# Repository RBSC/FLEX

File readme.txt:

--------------------------------------------
MSX FLEX Slot Extender v1.1
Copyright (c) 2019 RBSC
--------------------------------------------
Last updated: June 14, 2019
--------------------------------------------

WARNING! To avoid damage to FLEX and your MSX computer never insert or remove the extender when a computer is powered on!

WARNING! The extender is not designed to supply the power to more than one cartridge. If a slot expander is connected to
FLEX, it must have its own power supply!

IMPORTANT NOTE! The RBSC can not be sure that FLEX will work flawlessly with all available MSX hardware. See the "Known
issues" section below for more info.

About
-----

The device is the simple extender of the 50-pin MSX slot or MSX bus. It consists of 3 parts - the cartridge part, the 50-pin
slot extender and the 60-pin slot extender modules. The modules are connected to each other with the 50-wire ribbon cable
that is approximately 30cm long. 

The data lines have 100 Ohm resistors installed to compensate for the wave impedance of the ribbon cable. A few 100nf ceramic
capacitors are installed between the +5v and ground signals to remove the possible interferences in power lines.

The FLEX is designed to be used with one cartridge or one 60-pin module at a time. The cartridge board has 2 placeholders
for 50-pin ribbon cable connectors and this allows to attach 2 cables at the same time and to connect the 50 and 60-pin
extenders simultaneously. But those must never have 2 devices inserted at the same time! Doing this may create conflicts and
cause a power surge!

Cases
-----

The models of the cases and their covers must be printed with 0.2mm layer height and with their open sides facing upwards. The
pin is printed vertically and then is glued into the 50-pin extender's case. Brim is recommended for all models. The supports
must be at 20%. The infill must be not lower than 25%. The sturdy PLA is recommended for the cases.

The cartridge module's cover is attached to its case with 2 conical head screws (2.0mm x 12.0mm). The extender modules' covers
are attached to their cases with 4 conical head screws (3.0mm x 20.0mm). Shorter and longer screws must not be used. The screws
could be bought in any decent hardware store.

Engraving
---------

When the cases are printed in black plastic, the "MSX FLEX" text will not be visible on the top of the cases. In this case we
recommend to do laser engraving. The images for laser engraving are attached. The recommended width of the engraving should
not exceed 60mm. The recommended depth of engraving should be 0.1mm. See the "ready_engraved.jpg" picture for the reference.

The engraving must not be done in the areas where the "MSX FLEX" test is present, see the "ready.jpg" image for the reference.
Engraving in the areas where the text is located will result in damaging the thin layer of plastic above the letters and ruin
the good look of the case!

Notes
-----

The boards inside the cartridge case and the 60-pin extender case may wobble a bit. This was designed like that on purpose.
Please do not try to fix the boards firmly. Such wobbling makes the insertion and removal of the cables and devices safer.

Please note that the ribbon cable's connector is made out of plastic, so it's relatively fragile. When pulling the cable out
of the cartridge module please be gentle and do not pull too hard. When removing the cable please try to avoid bending of
the pins on the cartridge board. If the pins are bent, try to carefully straighten them with pliers before inserting the
cable.

The key on the flat ribbon's 50-pin connector may not be compatible with MSX bus expansion connectors of certain MSX computers.
So if you are connecting FLEX to the expansion bus connector, please make sure that the cable's connector is properly aligned.
In some cases the key will need to be removed for the proper alignment, however we advise against it. Be warned, that incorrect
orientation of the FLEX connector may cause severe damage to your MSX computer!

The cases of FLEX modules are normally made out of PLA plastic that is rather fragile. So when disassembling and reassembling
the cases please do not tighten the screws too much or you risk to damage the threads inside the screw holes. If that happens,
fixing the problem would require inserting a few thin threads of PLA into the hole before using the screw.

The SW1 and SW2 pins on the extender modules are not connected to each other. So on MSXs that require those pins to be
shortened in order to enable the power supply, inserting the FLEX with any of its slot extenders will not power-up the computer.
Only when a cartridge or a side slot module is inserted into one of the extender modules, the computer will power-up.

Known issues
------------

The FLEX may not work 100% reliably with all available MSX hardware. We've tested it on Yamaha, Philips, Panasonic, Sanyo and
Toshiba computers and there were a few minor issues that were depending on the hardware of those MSX machines or/and the
devices used in the extender.

We noticed the problem on certain computers with OPLL playback with the GR8NET cartridge. And we had a total failure of FLEX
with RBSC's IDE-FDD cartridge on all MSXs. This cartridge with the Sunrise BIOS complained about data corruption with most of
our CF cards. With other cards it worked, but frequent crashes occurred. So we don't recommend to use FLEX with the IDE-FDD
cartridge.

Tools
-----

The following IDC crimping tool should be used to make the cables:
https://www.aliexpress.com/item/Flat-Ribbon-Cable-Connector-Fixture-IDC-Crimping-Tool-DIY/32792508854.html

The tool requires the special adapter for the male IDC connectors:
https://www.ebay.de/itm/2pc-Adaptor-for-IDC-DIP-Plug-Crimping-tool-HT-214D-Crimper-Width-0-1-0-3-0-6/131173729141

Or you can print the adapter yourself:
https://www.thingiverse.com/thing:3504332

IMPORTANT!
----------

The RBSC provides all the files and information for free, without any liability (see the disclaimer.txt file). The provided
information, software or hardware must not be used for commercial purposes unless permitted by the RBSC. Producing a small
amount of boards for personal projects and selling the rest of the batch is allowed without the permission of RBSC. Printing
of cases is allowed without limitation.

When the boards and 3D models are used to create alternative projects, please always mention the original source and the
copyright!

Contact information
-------------------

The members of RBSC group Wierzbowsky, Tnt23, Ptero, Pencioner and DJS3000 can be contacted via the MSX.ORG or ZX-PK.RU forums.
Just send a personal message and state your business.

The RBSC repository can be found here:

https://github.com/rbsc

The MSX-related 3D models published by RBSC can be found here:

https://www.thingiverse.com/groups/rbsc/things

-= ! MSX FOREVER ! =-

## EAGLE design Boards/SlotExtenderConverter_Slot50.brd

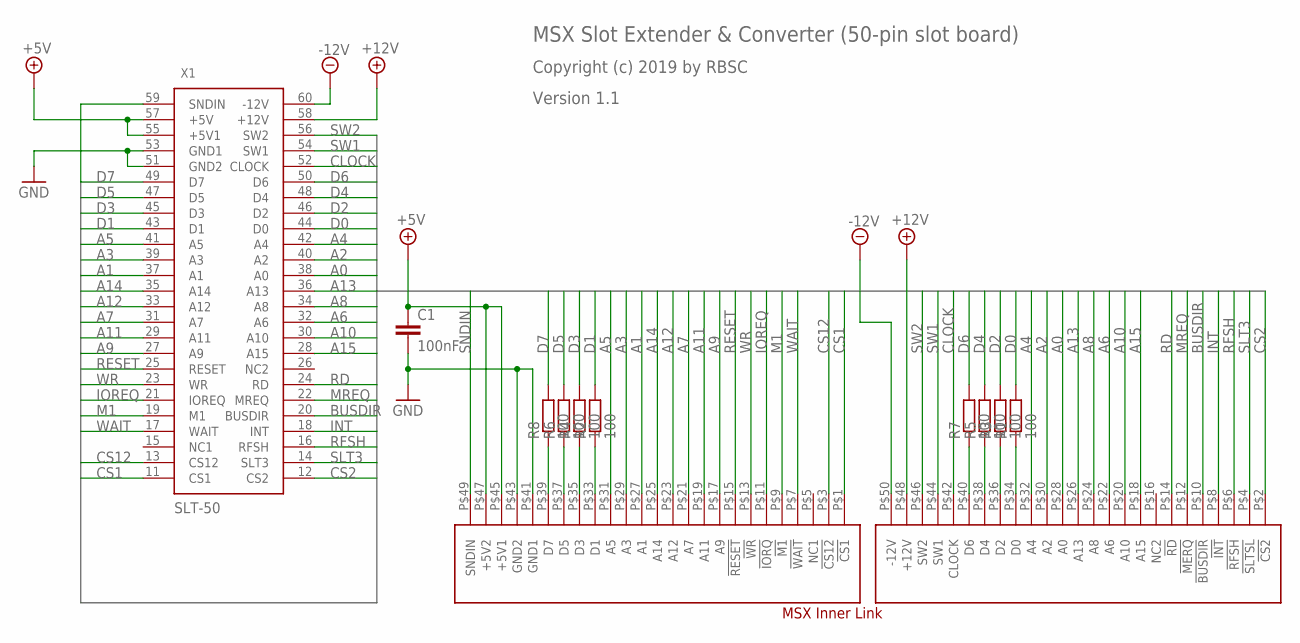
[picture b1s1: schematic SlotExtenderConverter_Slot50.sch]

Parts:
C1: 100nF; C0805K
CN3: MSX_INNER_LINK
R1, R2, R3, R4, R5, R6, R7, R8: 100; M0805
X1: SLT-50

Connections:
+5V: C1.1, CN3.P$45 (+5V1), CN3.P$47 (+5V2), X1.55 (+5V1), X1.57 (+5V)
+12V: CN3.P$48 (+12V), X1.58 (+12V)
-12V: CN3.P$50 (-12V), X1.60 (-12V)
A0: CN3.P$28 (A0), X1.38 (A0)
A1: CN3.P$27 (A1), X1.37 (A1)
A2: CN3.P$30 (A2), X1.40 (A2)
A3: CN3.P$29 (A3), X1.39 (A3)
A4: CN3.P$32 (A4), X1.42 (A4)
A5: CN3.P$31 (A5), X1.41 (A5)
A6: CN3.P$22 (A6), X1.32 (A6)
A7: CN3.P$21 (A7), X1.31 (A7)
A8: CN3.P$24 (A8), X1.34 (A8)
A9: CN3.P$17 (A9), X1.27 (A9)
A10: CN3.P$20 (A10), X1.30 (A10)
A11: CN3.P$19 (A11), X1.29 (A11)
A12: CN3.P$23 (A12), X1.33 (A12)
A13: CN3.P$26 (A13), X1.36 (A13)
A14: CN3.P$25 (A14), X1.35 (A14)
A15: CN3.P$18 (A15), X1.28 (A15)
BUSDIR: CN3.P$10 (!BUSDIR), X1.20 (BUSDIR)
CLOCK: CN3.P$42 (CLOCK), X1.52 (CLOCK)
CS1: CN3.P$1 (!CS1), X1.11 (CS1)
CS2: CN3.P$2 (!CS2), X1.12 (CS2)
CS12: CN3.P$3 (!CS12), X1.13 (CS12)
D0: R1.2, X1.44 (D0)
D1: R2.2, X1.43 (D1)
D2: R3.2, X1.46 (D2)
D3: R4.2, X1.45 (D3)
D4: R5.2, X1.48 (D4)
D5: R6.2, X1.47 (D5)
D6: R7.2, X1.50 (D6)
D7: R8.2, X1.49 (D7)
GND: C1.2, CN3.P$41 (GND1), CN3.P$43 (GND2), X1.51 (GND2), X1.53 (GND1)
INT: CN3.P$8 (!INT), X1.18 (INT)
IOREQ: CN3.P$11 (!IORQ), X1.21 (IOREQ)
M1: CN3.P$9 (!M1), X1.19 (M1)
MREQ: CN3.P$12 (!MERQ), X1.22 (MREQ)
unnamed: CN3.P$40 (D6), R7.1
unnamed: CN3.P$39 (D7), R8.1
unnamed: CN3.P$37 (D5), R6.1
unnamed: CN3.P$35 (D3), R4.1
unnamed: CN3.P$33 (D1), R2.1
unnamed: CN3.P$38 (D4), R5.1
unnamed: CN3.P$36 (D2), R3.1
unnamed: CN3.P$34 (D0), R1.1
RD: CN3.P$14 (!RD), X1.24 (RD)
RESET: CN3.P$15 (!RESET), X1.25 (RESET)
RFSH: CN3.P$6 (!RFSH), X1.16 (RFSH)
SLT3: CN3.P$4 (!SLTSL), X1.14 (SLT3)
SNDIN: CN3.P$49 (SNDIN), X1.59 (SNDIN)
SW1: CN3.P$44 (SW1), X1.54 (SW1)
SW2: CN3.P$46 (SW2), X1.56 (SW2)
WAIT: CN3.P$7 (!WAIT), X1.17 (WAIT)
WR: CN3.P$13 (!WR), X1.23 (WR)

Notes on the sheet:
MSX Slot Extender & Converter (50-pin slot board)
Copyright (c) 2019 by RBSC
Version 1.1

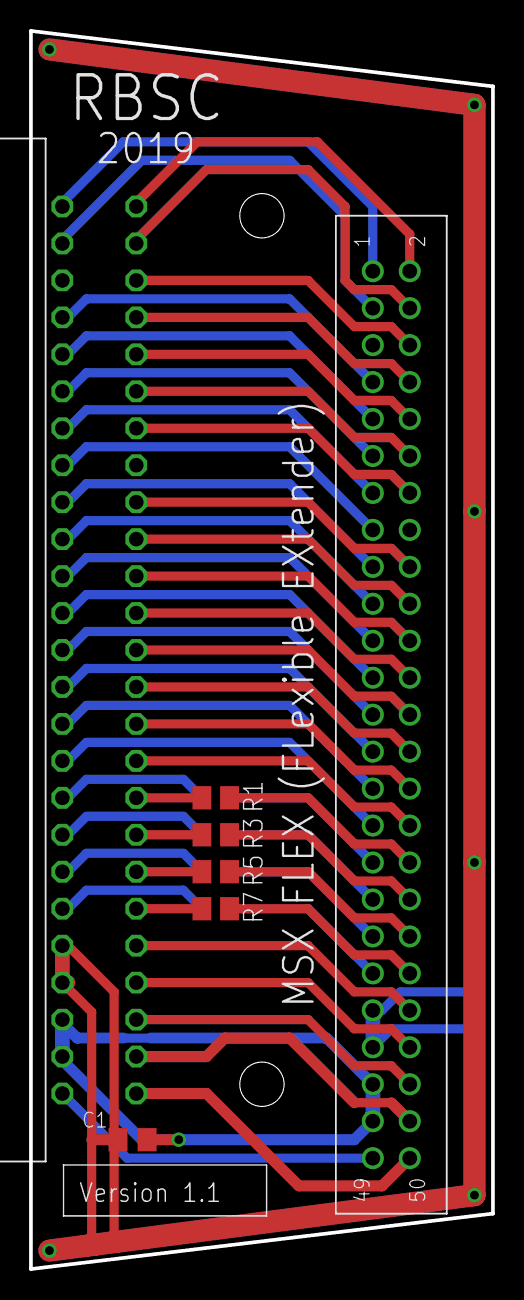
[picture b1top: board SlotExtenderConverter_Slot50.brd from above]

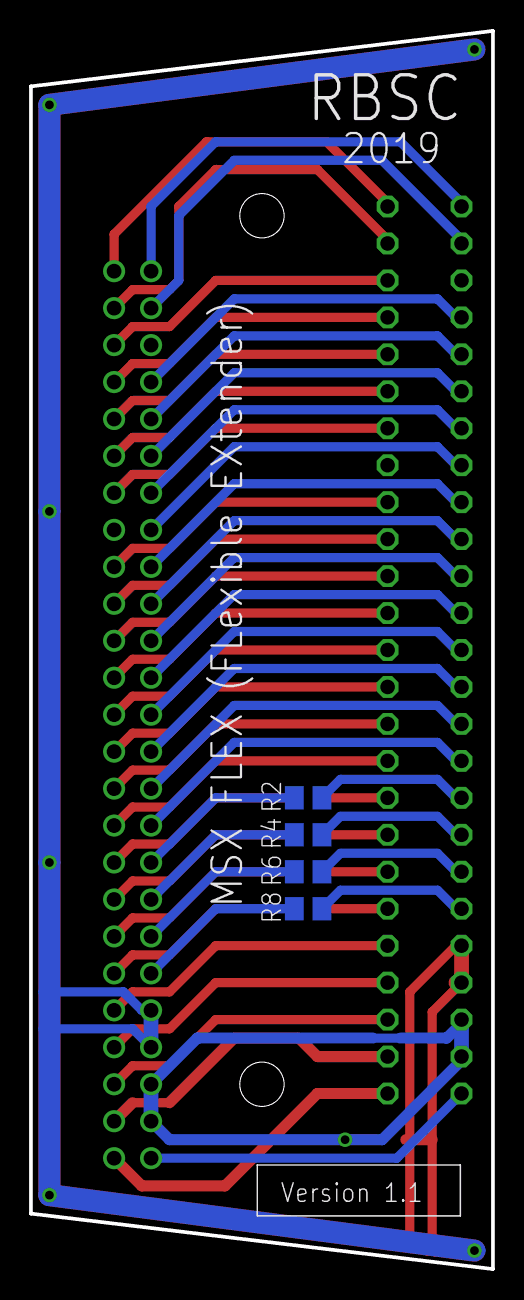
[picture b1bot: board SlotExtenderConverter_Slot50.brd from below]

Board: 2 copper layers, 31.8 x 85.1 mm, 11 parts (5 on the bottom side), 54 nets.

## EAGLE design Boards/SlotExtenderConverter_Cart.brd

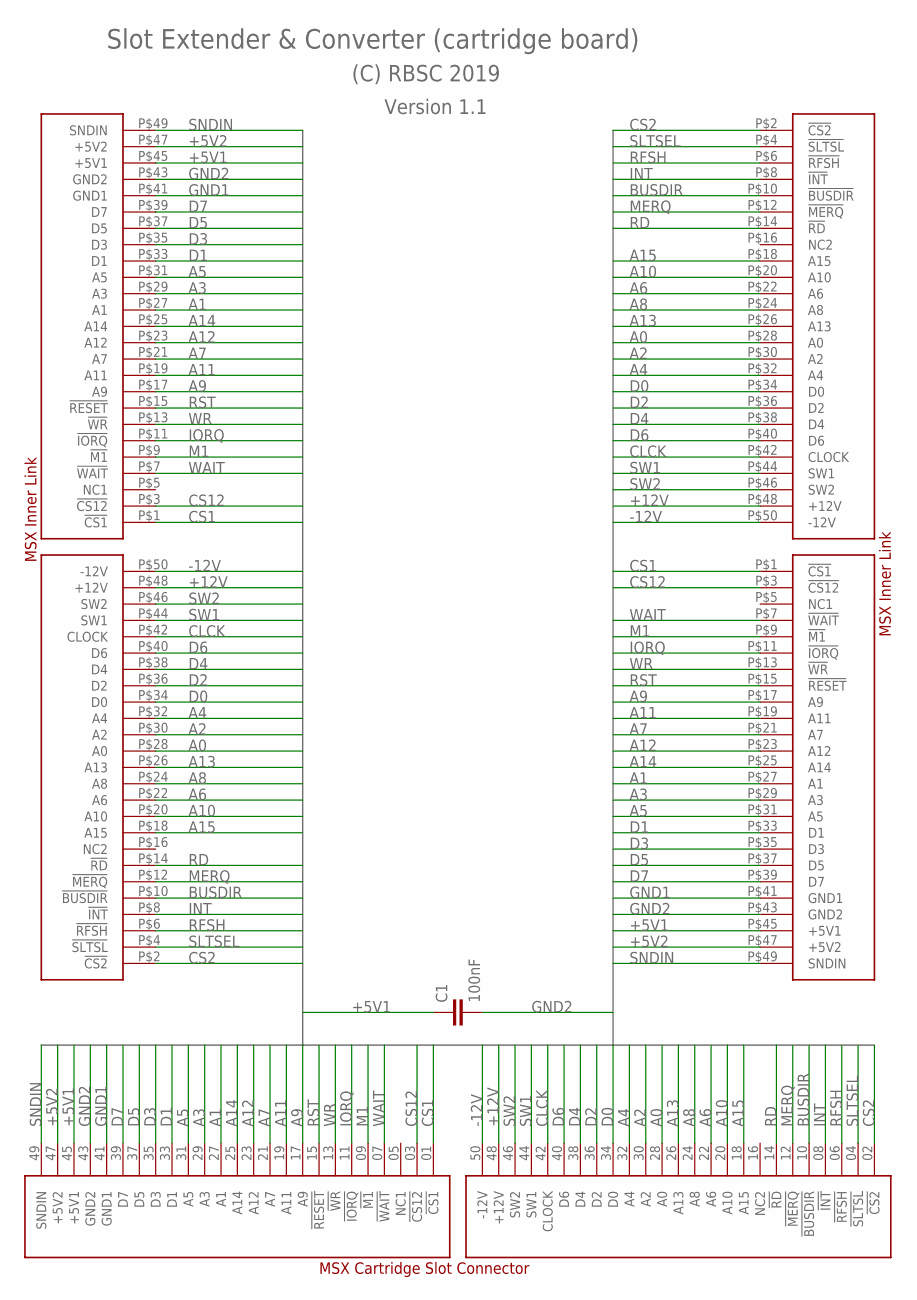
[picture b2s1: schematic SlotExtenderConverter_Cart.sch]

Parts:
C1: 100nF; C0805K
CN1: MSX_SLOT_CON
CN2, CN3: MSX_INNER_LINK

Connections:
+5V1: C1.1, CN1.45 (+5V1), CN2.P$45 (+5V1), CN3.P$45 (+5V1)
+5V2: CN1.47 (+5V2), CN2.P$47 (+5V2), CN3.P$47 (+5V2)
+12V: CN1.48 (+12V), CN2.P$48 (+12V), CN3.P$48 (+12V)
-12V: CN1.50 (-12V), CN2.P$50 (-12V), CN3.P$50 (-12V)
A0: CN1.28 (A0), CN2.P$28 (A0), CN3.P$28 (A0)
A1: CN1.27 (A1), CN2.P$27 (A1), CN3.P$27 (A1)
A2: CN1.30 (A2), CN2.P$30 (A2), CN3.P$30 (A2)
A3: CN1.29 (A3), CN2.P$29 (A3), CN3.P$29 (A3)
A4: CN1.32 (A4), CN2.P$32 (A4), CN3.P$32 (A4)
A5: CN1.31 (A5), CN2.P$31 (A5), CN3.P$31 (A5)
A6: CN1.22 (A6), CN2.P$22 (A6), CN3.P$22 (A6)
A7: CN1.21 (A7), CN2.P$21 (A7), CN3.P$21 (A7)
A8: CN1.24 (A8), CN2.P$24 (A8), CN3.P$24 (A8)
A9: CN1.17 (A9), CN2.P$17 (A9), CN3.P$17 (A9)
A10: CN1.20 (A10), CN2.P$20 (A10), CN3.P$20 (A10)
A11: CN1.19 (A11), CN2.P$19 (A11), CN3.P$19 (A11)
A12: CN1.23 (A12), CN2.P$23 (A12), CN3.P$23 (A12)
A13: CN1.26 (A13), CN2.P$26 (A13), CN3.P$26 (A13)
A14: CN1.25 (A14), CN2.P$25 (A14), CN3.P$25 (A14)
A15: CN1.18 (A15), CN2.P$18 (A15), CN3.P$18 (A15)
BUSDIR: CN1.10 (!BUSDIR), CN2.P$10 (!BUSDIR), CN3.P$10 (!BUSDIR)
CLCK: CN1.42 (CLOCK), CN2.P$42 (CLOCK), CN3.P$42 (CLOCK)
CS1: CN1.01 (!CS1), CN2.P$1 (!CS1), CN3.P$1 (!CS1)
CS2: CN1.02 (!CS2), CN2.P$2 (!CS2), CN3.P$2 (!CS2)
CS12: CN1.03 (!CS12), CN2.P$3 (!CS12), CN3.P$3 (!CS12)
D0: CN1.34 (D0), CN2.P$34 (D0), CN3.P$34 (D0)
D1: CN1.33 (D1), CN2.P$33 (D1), CN3.P$33 (D1)
D2: CN1.36 (D2), CN2.P$36 (D2), CN3.P$36 (D2)
D3: CN1.35 (D3), CN2.P$35 (D3), CN3.P$35 (D3)
D4: CN1.38 (D4), CN2.P$38 (D4), CN3.P$38 (D4)
D5: CN1.37 (D5), CN2.P$37 (D5), CN3.P$37 (D5)
D6: CN1.40 (D6), CN2.P$40 (D6), CN3.P$40 (D6)
D7: CN1.39 (D7), CN2.P$39 (D7), CN3.P$39 (D7)
GND1: CN1.41 (GND1), CN2.P$41 (GND1), CN3.P$41 (GND1)
GND2: C1.2, CN1.43 (GND2), CN2.P$43 (GND2), CN3.P$43 (GND2)
INT: CN1.08 (!INT), CN2.P$8 (!INT), CN3.P$8 (!INT)
IORQ: CN1.11 (!IORQ), CN2.P$11 (!IORQ), CN3.P$11 (!IORQ)
M1: CN1.09 (!M1), CN2.P$9 (!M1), CN3.P$9 (!M1)
MERQ: CN1.12 (!MERQ), CN2.P$12 (!MERQ), CN3.P$12 (!MERQ)
RD: CN1.14 (!RD), CN2.P$14 (!RD), CN3.P$14 (!RD)
RFSH: CN1.06 (!RFSH), CN2.P$6 (!RFSH), CN3.P$6 (!RFSH)
RST: CN1.15 (!RESET), CN2.P$15 (!RESET), CN3.P$15 (!RESET)
SLTSEL: CN1.04 (!SLTSL), CN2.P$4 (!SLTSL), CN3.P$4 (!SLTSL)
SNDIN: CN1.49 (SNDIN), CN2.P$49 (SNDIN), CN3.P$49 (SNDIN)
SW1: CN1.44 (SW1), CN2.P$44 (SW1), CN3.P$44 (SW1)
SW2: CN1.46 (SW2), CN2.P$46 (SW2), CN3.P$46 (SW2)
WAIT: CN1.07 (!WAIT), CN2.P$7 (!WAIT), CN3.P$7 (!WAIT)
WR: CN1.13 (!WR), CN2.P$13 (!WR), CN3.P$13 (!WR)

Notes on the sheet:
Slot Extender & Converter (cartridge board)
(C) RBSC 2019
Version 1.1

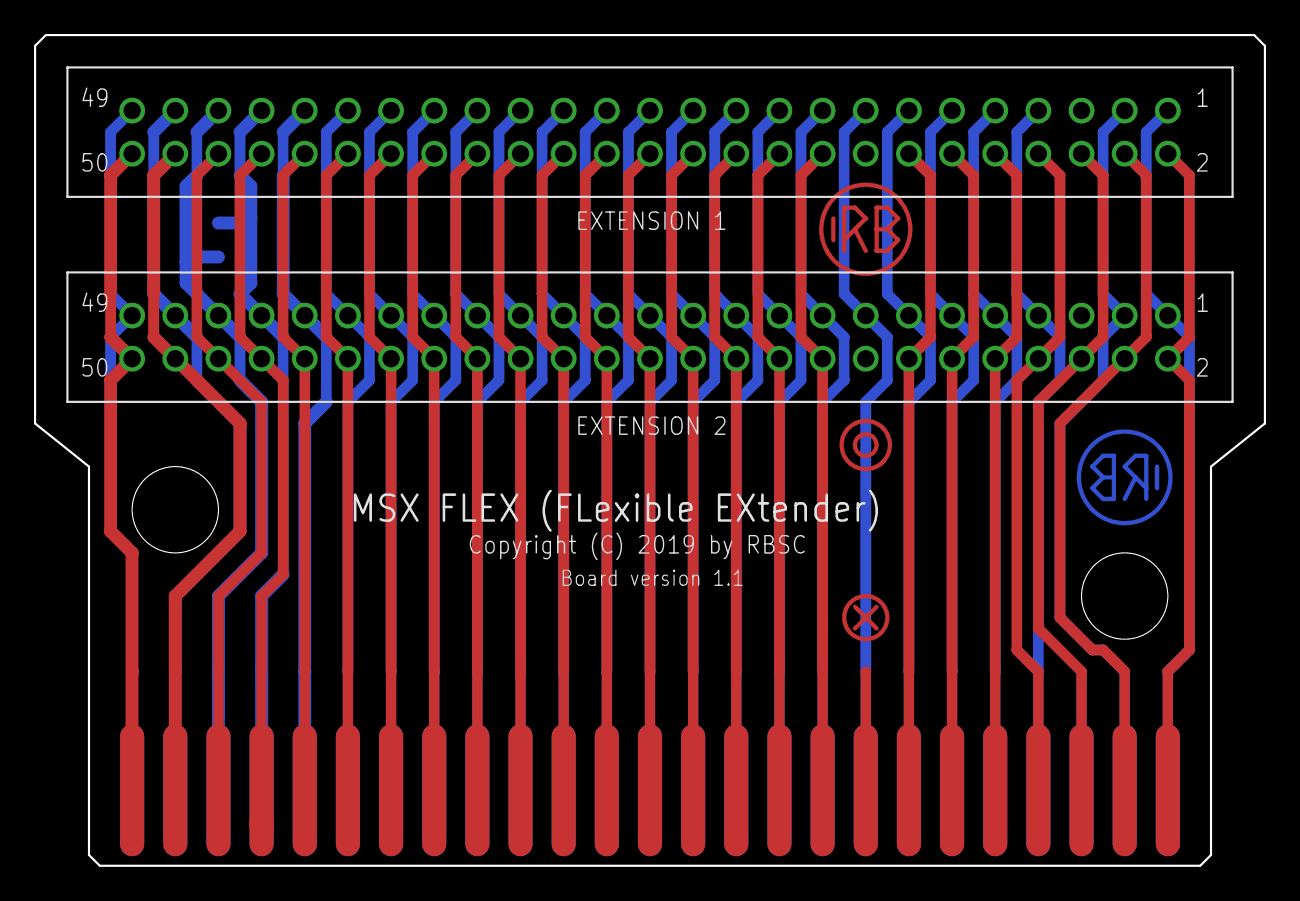
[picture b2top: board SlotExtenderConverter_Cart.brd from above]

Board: 2 copper layers, 72.4 x 48.9 mm, 4 parts (1 on the bottom side), 48 nets.

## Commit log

2019-06-14 :space_invader: Added .gitattributes & .gitignore files
2019-06-14 Initial release 14.06.2019
    Initial release of FLEX project
2019-08-15 Updated 15.08.2019
    Updated readme
2020-02-20 Logo update
